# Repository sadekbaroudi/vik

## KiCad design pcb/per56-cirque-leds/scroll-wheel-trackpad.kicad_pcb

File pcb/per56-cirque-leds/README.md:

# PER56 Scroll Ring with Cirque Trackpad and LEDs

## Overview

This is a VIK module designed to mount a [PER56 scroll ring](https://www.mouser.com/new/bourns/bourns-per56-incremental-ring-encoders/), with a 35mm [Cirque Trackpad](https://www.cirque.com/glidepoint-circle-trackpads) and optional WS2812B LEDs.

This was used to demonstrate a build for [vulpes minora](https://github.com/sadekbaroudi/vulpes-minora). See the repo for pictures.

## Fabrication and BOM

For PCB fabrication, you can use the files in the production folder.

* gerbers.zip - the file used to fabricate the pcb
* bom.csv - used for PCBA. You can also use the part numbers in this file to look up the exact parts as [lcsc.com](https://lcsc.com)
* positions.csv - used for PCBA

Using the 3 files above, this has been tested at [jlcpcb.com](https://jlcpcb.com)

## VIK module certification

| Category                | Classification          | Response           |
| ----------------------- | ----------------------- | ------------------ |
| FPC connector           | Required                | :heavy_check_mark: |
| Breakout pins           | Recommended             | :x:                |
| Uses: SPI               | Optional                | :heavy_check_mark: |
| SPI used for SPI only   | Strongly recommended    | :heavy_check_mark: |
| Uses: I2C               | Optional                | :x:                |
| I2C used for I2C only   | Strongly Recommended    | N/A                |
| I2C pull ups            | Required                | N/A                |
| Uses: RGB               | Optional                | :heavy_check_mark: |
| Uses: Extra GPIO 1      | Optional                | :heavy_check_mark: |
| Uses: Extra GPIO 2      | Optional                | :heavy_check_mark: |
| Standard PCB Size/Mount | Strongly recommended    | Large              |

## PCB images

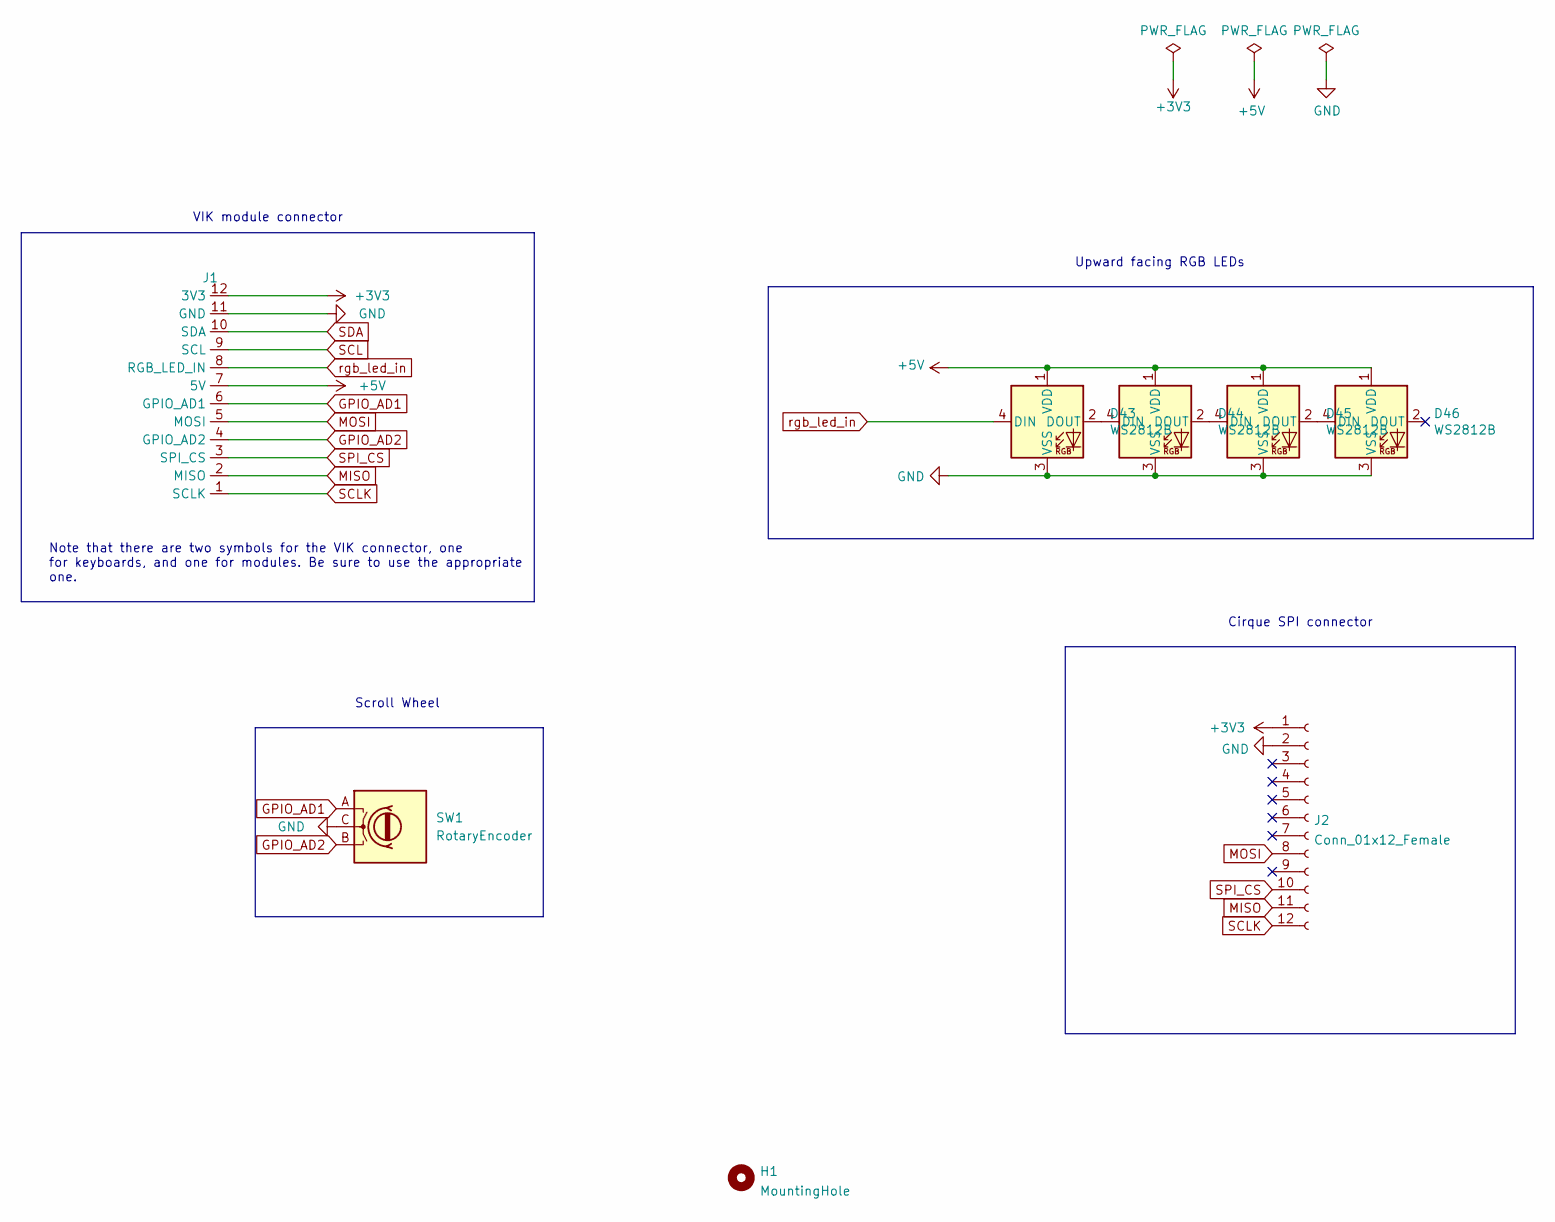
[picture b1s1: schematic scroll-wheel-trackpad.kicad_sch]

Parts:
D43, D44, D45, D46: WS2812B; LED_WS2812B_PLCC4_5.0x5.0mm_P3.2mm-reversible; LCSC C2761795
H1: MountingHole; vik-module-mounting-large
J1: vik-module-connector-horizontal; LCSC C479750
J2: Conn_01x12_Female; FPC-SMD_FPC05012-09200-.5mm-rev; LCSC C479750
SW1: RotaryEncoder; PERS56v3

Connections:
+3V3: J1.12 (3V3), J2.1
+5V: D43.1 (VDD), D44.1 (VDD), D45.1 (VDD), D46.1 (VDD), J1.7 (5V)
GND: D43.3 (VSS), D44.3 (VSS), D45.3 (VSS), D46.3 (VSS), J1.11 (GND), J2.2, SW1.C
GPIO_AD1: J1.6 (GPIO_AD1), SW1.A
GPIO_AD2: J1.4 (GPIO_AD2), SW1.B
MISO: J1.2 (MISO), J2.11
MOSI: J1.5 (MOSI), J2.8
unnamed: D43.2 (DOUT), D44.4 (DIN)
unnamed: D44.2 (DOUT), D45.4 (DIN)
unnamed: D45.2 (DOUT), D46.4 (DIN)
SCL: J1.9 (SCL)
SCLK: J1.1 (SCLK), J2.12
SDA: J1.10 (SDA)
SPI_CS: J1.3 (SPI_CS), J2.10
rgb_led_in: D43.4 (DIN), J1.8 (RGB_LED_IN)

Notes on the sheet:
Cirque SPI connector
Upward facing RGB LEDs
VIK module connector
Note that there are two symbols for the VIK connector, one for keyboards, and one for modules. Be sure to use the appropriate one.
Scroll Wheel

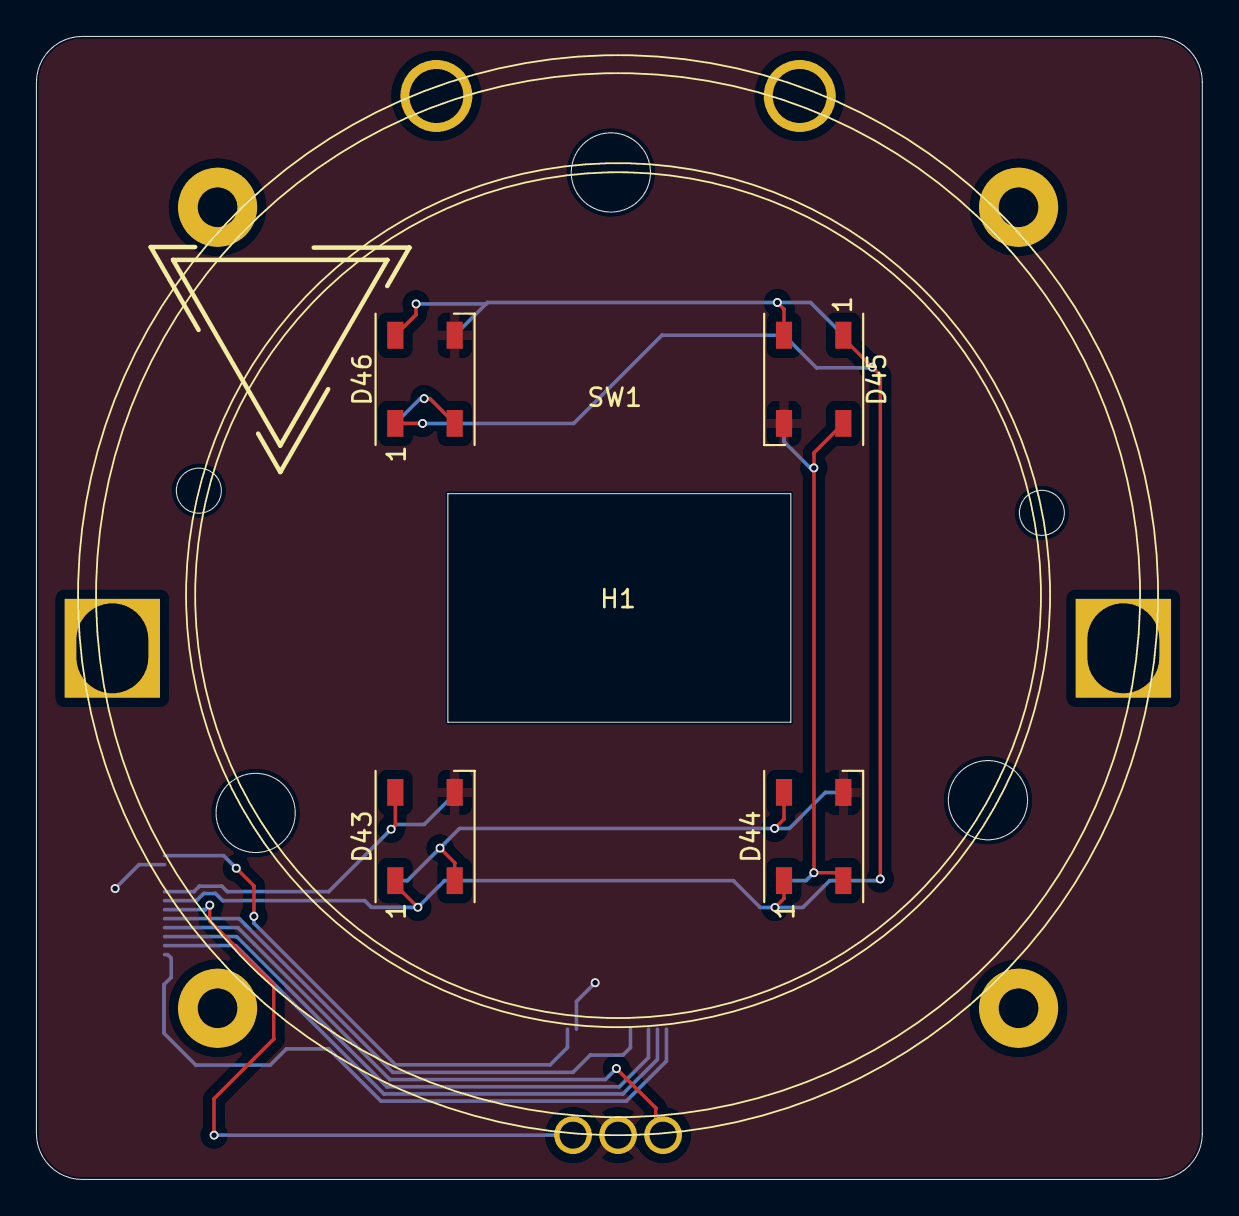
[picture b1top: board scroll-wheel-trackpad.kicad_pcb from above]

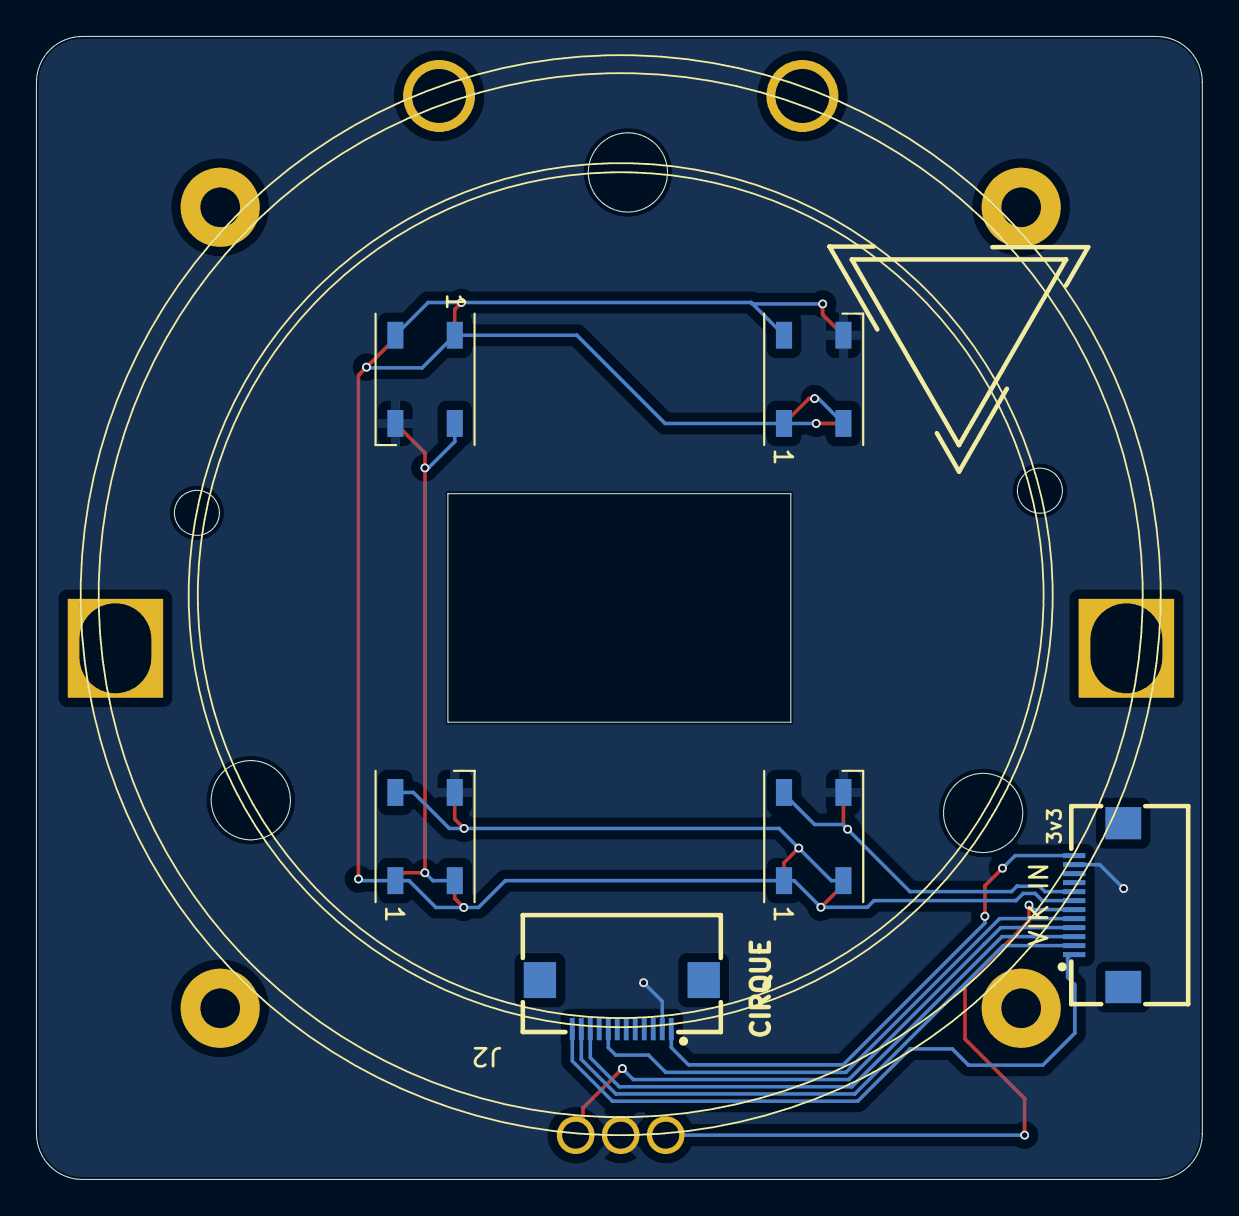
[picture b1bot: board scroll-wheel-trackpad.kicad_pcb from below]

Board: 2 copper layers, 64.8 x 63.5 mm, 8 parts (2 on the bottom side), 13 nets.

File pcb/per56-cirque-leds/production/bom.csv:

Designator,Footprint,Quantity,Value,LCSC Part #
"D43, D44, D45, D46",LED_WS2812B_PLCC4_5.0x5.0mm_P3.2mm-reversible,4,WS2812B,C2761795
H1,vik-module-mounting-large,1,MountingHole,
J1,vik-module-connector-horizontal,1,~,C479750
J2,FPC-SMD_FPC05012-09200-.5mm-rev,1,Conn_01x12_Female,C479750
SW1,PERS56v3,1,RotaryEncoder,

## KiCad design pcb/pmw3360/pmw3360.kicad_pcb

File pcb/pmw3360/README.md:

# PMW3360 trackball pcb

## Overview

This is a VIK module to use a PMW3360 motion sensor. This sensor is primarily used for mousing applications, and is supported in [QMK](https://github.com/qmk_firmware/qmk)

The most common use in the keyboard community is for trackballs.

Note that while I2C, RGB, and extra GPIO are broken out, but are not used in the circuitry, so they are not needed for the sensor. There are also footprints for I2C pull up resistors, which are also not needed, as I2C is not used.

## Fabrication and BOM

For PCB fabrication, you can use the files in the production folder.

* gerbers.zip - the file used to fabricate the pcb
* bom.csv - used for PCBA. You can also use the part numbers in this file to look up the exact parts as [lcsc.com](https://lcsc.com)
* positions.csv - used for PCBA

Using the 3 files above, this has been tested at [jlcpcb.com](https://jlcpcb.com)

## VIK module certification

| Category                | Classification          | Response           |
| ----------------------- | ----------------------- | ------------------ |
| FPC connector           | Required                | :heavy_check_mark: |
| Breakout pins           | Recommended             | :heavy_check_mark: |
| Uses: SPI               | Optional                | :heavy_check_mark: |
| SPI used for SPI only   | Strongly recommended    | :heavy_check_mark: |
| Uses: I2C               | Optional                | :x:                |
| I2C used for I2C only   | Strongly Recommended    | :x:                |
| I2C pull ups            | Required                | N/A                |
| Uses: RGB               | Optional                | :x:                |
| Uses: Extra GPIO 1      | Optional                | :x:                |
| Uses: Extra GPIO 2      | Optional                | :x:                |
| Standard PCB Size/Mount | Strongly recommended    | Small              |

## PCB images

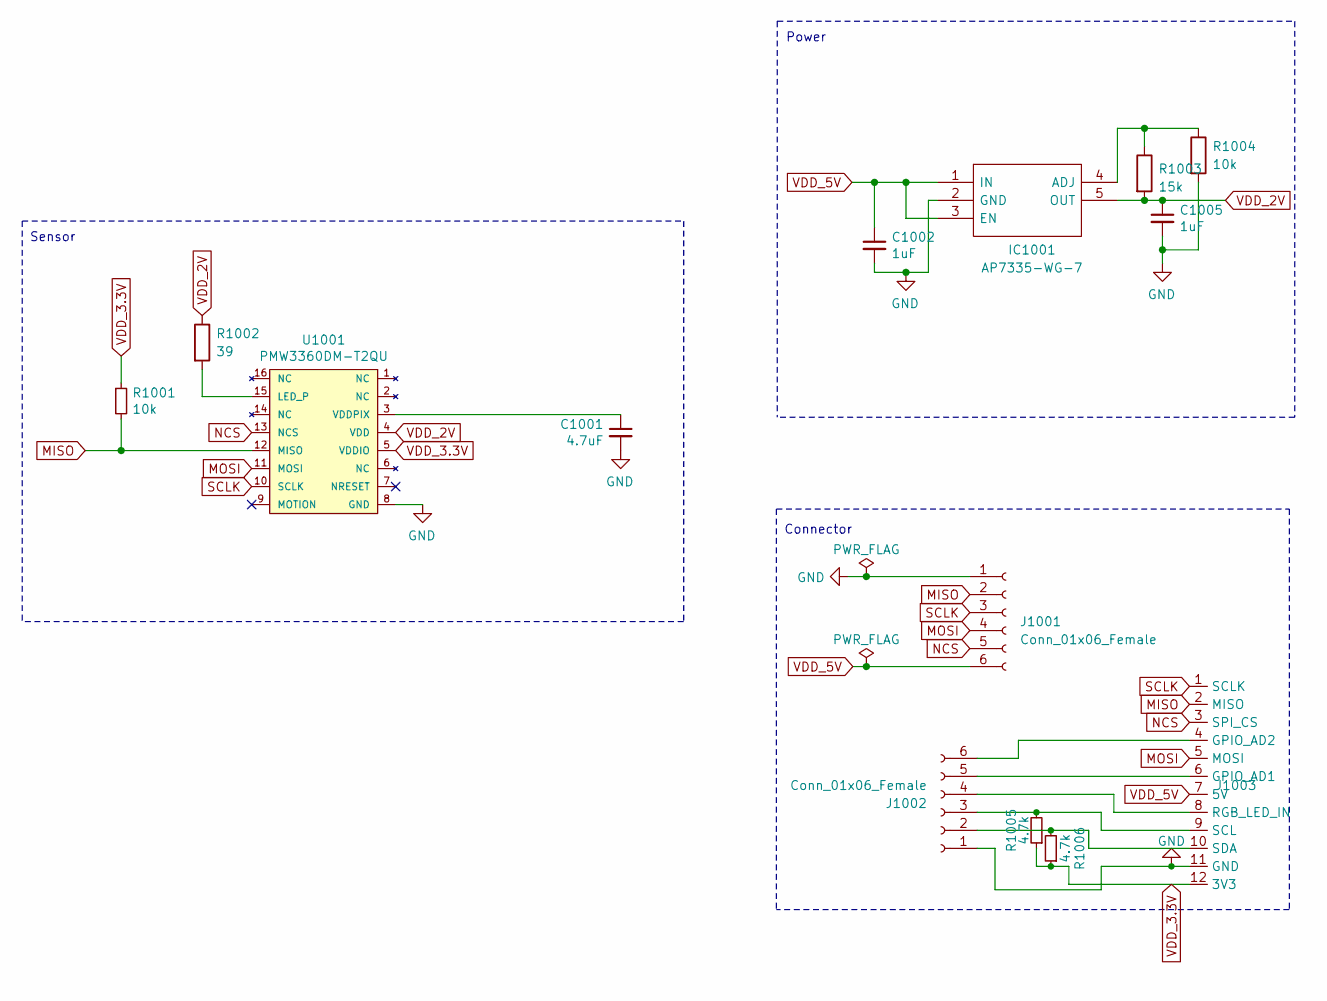
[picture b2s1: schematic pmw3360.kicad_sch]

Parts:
C1001: 4.7uF; C_0603_1608Metric; LCSC C19666
C1002, C1005: 1uF; C_0603_1608Metric; LCSC C15849
IC1001: AP7335-WG-7; SOT-23-5_HandSoldering; Manufacturer_Part_Number AP7331-WG-7; Mouser Part Number 621-AP7331-WG-7
J1001, J1002: Conn_01x06_Female; PinHeader_1x06_P2.54mm_Vertical
J1003: vik-module-connector-horizontal; LCSC C479750
R1001, R1004: 10k; R_0603_1608Metric; LCSC C25804
R1002: 39; R_0603_1608Metric; LCSC C23154
R1003: 15k; R_0603_1608Metric; LCSC C22809
R1005, R1006: 4.7k; D3_TH_SMD
U1001: PMW3360DM-T2QU; DIP-16_W10.16mm

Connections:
GND: C1001.2, C1002.2, C1005.2, IC1001.2 (GND), J1001.1, J1002.1, J1003.11 (GND), R1004.2, U1001.8 (GND)
MISO: J1001.2, J1003.2 (MISO), R1001.2, U1001.12 (MISO)
MOSI: J1001.4, J1003.5 (MOSI), U1001.11 (MOSI)
NCS: J1001.5, J1003.3 (SPI_CS), U1001.13 (NCS)
unnamed: IC1001.4 (ADJ), R1003.1, R1004.1
unnamed: J1002.2, J1003.10 (SDA), R1006.2
unnamed: J1002.3, J1003.9 (SCL), R1005.2
unnamed: J1002.4, J1003.8 (RGB_LED_IN)
unnamed: J1002.5, J1003.6 (GPIO_AD1)
unnamed: J1002.6, J1003.4 (GPIO_AD2)
unnamed: R1002.2, U1001.15 (LED_P)
unnamed: C1001.1, U1001.3 (VDDPIX)
SCLK: J1001.3, J1003.1 (SCLK), U1001.10 (SCLK)
VDD_2V: C1005.1, IC1001.5 (OUT), R1002.1, R1003.2, U1001.4 (VDD)
VDD_3.3V: J1003.12 (3V3), R1001.1, R1005.1, R1006.1, U1001.5 (VDDIO)
VDD_5V: C1002.1, IC1001.1 (IN), IC1001.3 (EN), J1001.6, J1003.7 (5V)

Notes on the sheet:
Power
Sensor
Connector

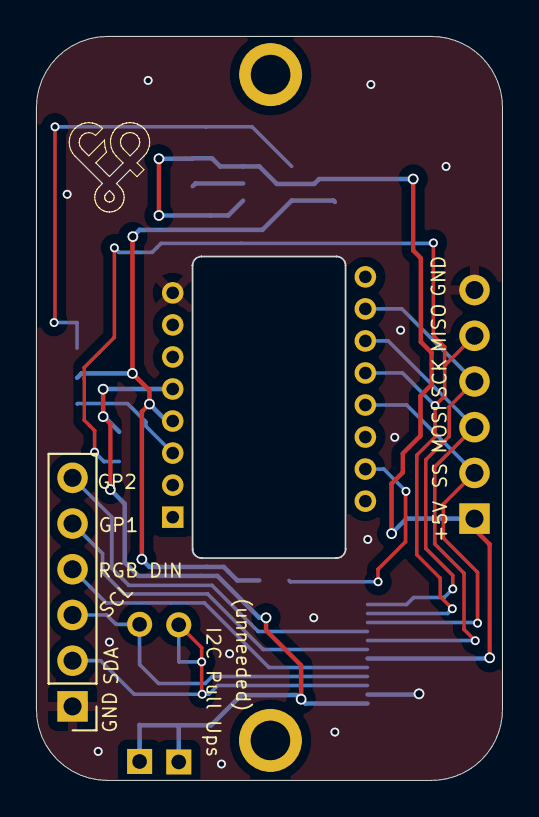
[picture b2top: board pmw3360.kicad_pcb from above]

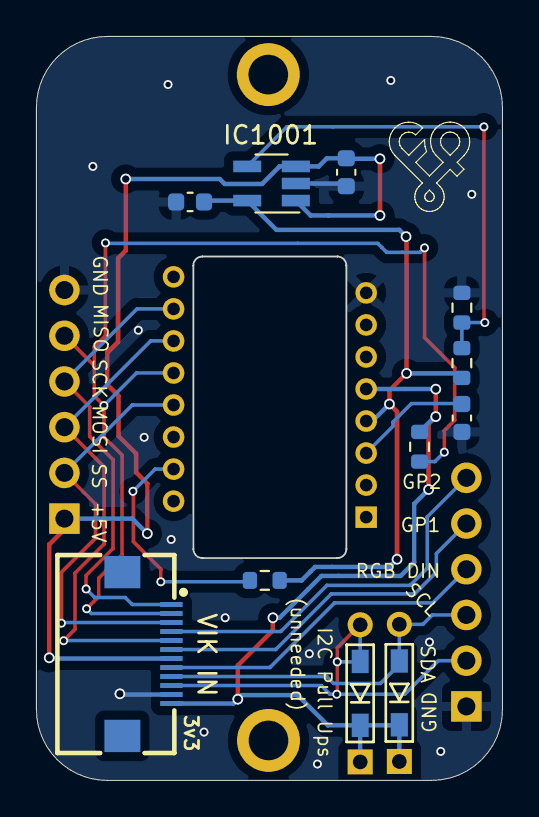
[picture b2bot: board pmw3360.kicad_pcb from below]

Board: 2 copper layers, 25.9 x 41.3 mm, 14 parts (12 on the bottom side), 16 nets.

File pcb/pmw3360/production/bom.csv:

Designator,Footprint,Quantity,Value,LCSC Part #
"_2, ",,2,,
C1001,0603,1,4.7uF,C19666
"C1002, C1005",0603,2,1uF,C15849
IC1001,SOT-23-5_HandSoldering,1,AP7335-WG-7,C460382
"J1001, J1002",PinHeader_1x06_P2.54mm_Vertical,2,Conn_01x06_Female,
J1003,vik-module-connector-horizontal,1,~,C479750
"R1001, R1004",0603,2,10k,C25804
R1002,0603,1,39,C23154
R1003,0603,1,15k,C22809
"R1005, R1006",D3_TH_SMD,2,4.7k,
U1001,DIP-16_W10.16mm,1,PMW3360DM-T2QU,

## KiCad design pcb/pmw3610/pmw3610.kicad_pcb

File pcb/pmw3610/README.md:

# PMW3610 trackball pcb

## Overview

This is a VIK module to use a PMW3610 motion sensor. This sensor is primarily used for mousing applications.

The most common use in the keyboard community is for trackballs.

Note that while I2C, RGB, and extra GPIO are broken out, but are not used in the circuitry, so they are not needed for the sensor. There are also footprints for I2C pull up resistors, which are also not needed, as I2C is not used.

There is a jumper for NRESET, with an option to:  
* Route to 3.3V, which means that it's inactive
* Route to the VIK GPIO 1, which allows you to control the state with the connected controller

You do not need to solder the jumper at all, since there is a weak pull up resistor in the PMW3610, but if you have any trouble with the state, and want to explicitly attach to 3.3V, you can.

## IMPORTANT

The PMW3610 sensor is a low power sensor, and uses serial data communication with a motion status pin (to reduce power consumption). This pcb uses the SPI pins, but is not standard SPI communication. This means that you cannot connect this module to a controller or board that uses the VIK SPI pins for any other purpose. These are being treated as standard GPIO for this module. This is not a VIK compliant module!

That said, if you understand the above, you can still use this module with no issues.

## Alternate parts

The LDO seems to be frequently out of stock at JLCPCB. The part number specified in this module is `C146366`. As an alternate part, you can try to use `C2862411` or `C2869109` (`TLV70019DDCR` or `TLV70019DDCT`, respectively)

## Fabrication and BOM

For PCB fabrication, you can use the files in the production folder.

* gerbers.zip - the file used to fabricate the pcb
* bom.csv - used for PCBA. You can also use the part numbers in this file to look up the exact parts as [lcsc.com](https://lcsc.com)
* positions.csv - used for PCBA

Using the 3 files above, this has been tested at [jlcpcb.com](https://jlcpcb.com)

## VIK module certification

| Category                | Classification          | Response           |
| ----------------------- | ----------------------- | ------------------ |
| FPC connector           | Required                | :heavy_check_mark: |
| Breakout pins           | Recommended             | :heavy_check_mark: |
| Uses: SPI               | Optional                | :heavy_check_mark: |
| SPI used for SPI only   | Strongly recommended    | :x:                |
| Uses: I2C               | Optional                | :x:                |
| I2C used for I2C only   | Strongly Recommended    | :x:                |
| I2C pull ups            | Required                | N/A                |
| Uses: RGB               | Optional                | :x:                |
| Uses: Extra GPIO 1      | Optional                | :x:                |
| Uses: Extra GPIO 2      | Optional                | :x:                |
| Standard PCB Size/Mount | Strongly recommended    | Small              |

## PCB images

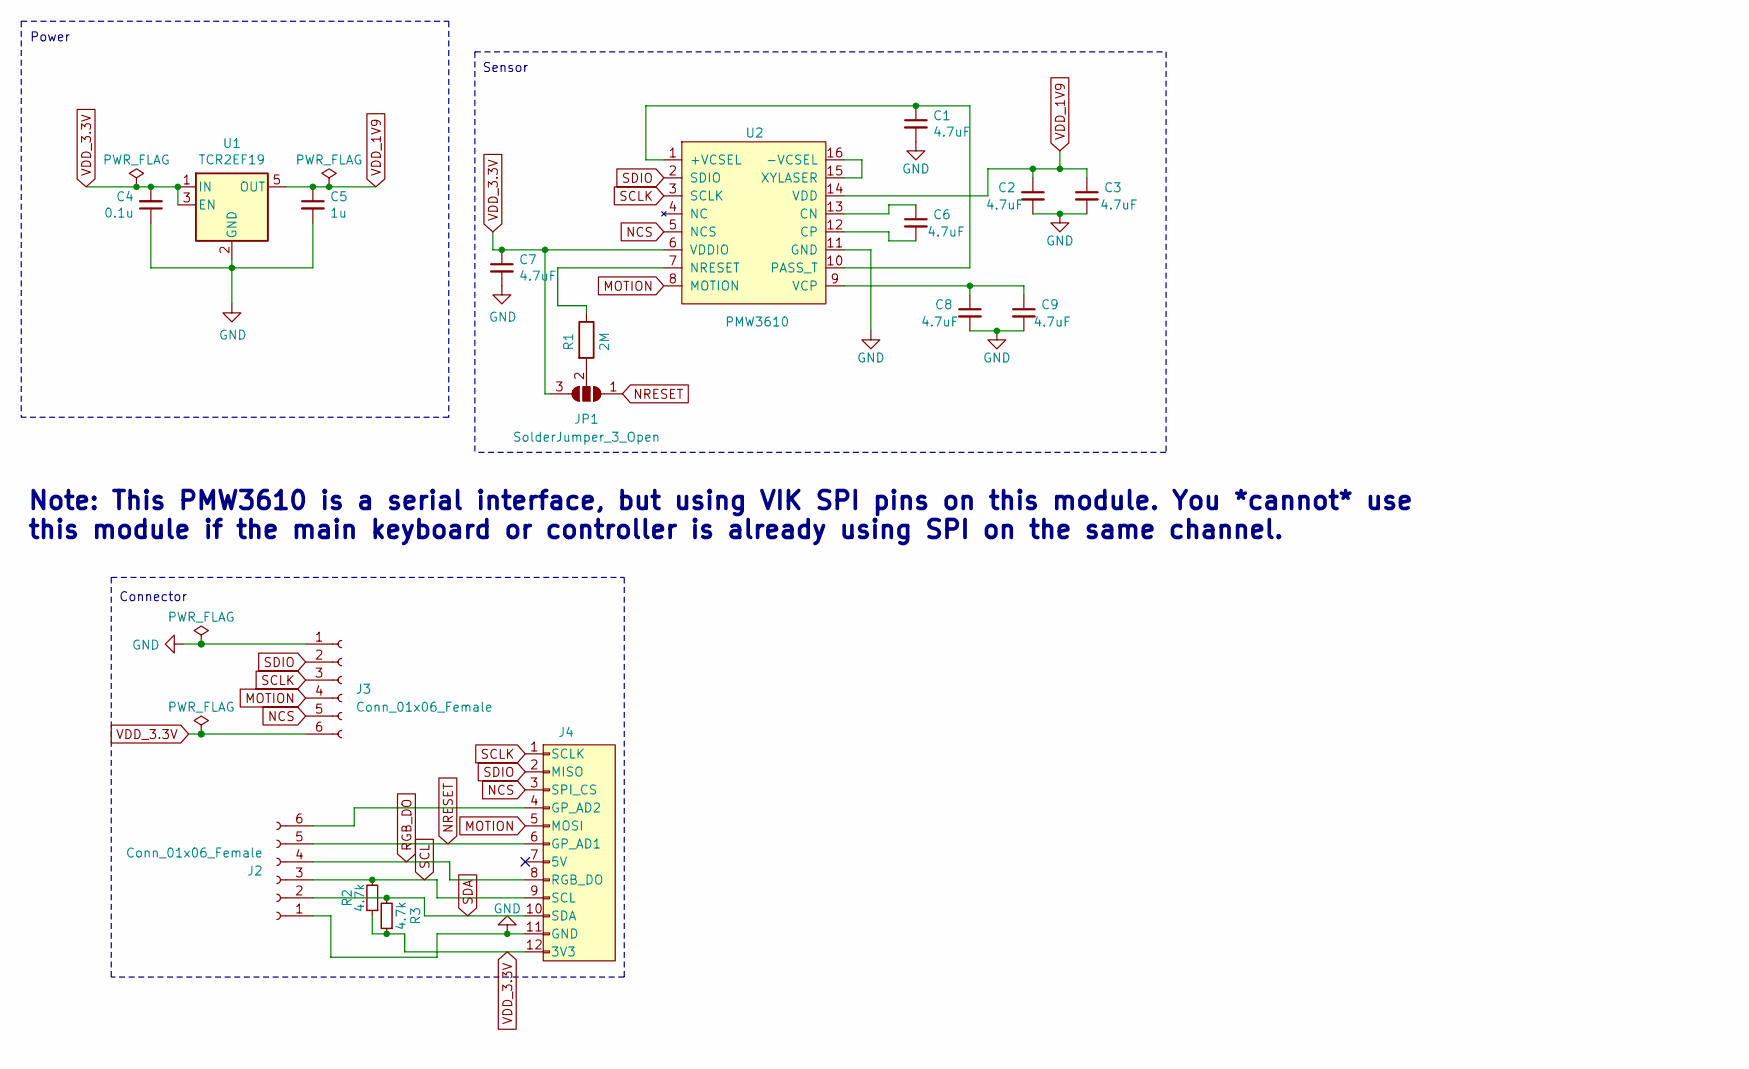
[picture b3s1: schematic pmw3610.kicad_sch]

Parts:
C1, C2, C3, C6, C7, C8, C9: 4.7uF; C_0603_1608Metric; LCSC C19666
C4: 0.1u; C_0603_1608Metric; LCSC C14663
C5: 1u; C_0603_1608Metric; LCSC C15849
J2, J3: Conn_01x06_Female; PinHeader_1x06_P2.54mm_Vertical
J4: vik-module-connector-horizontal; LCSC C479750
JP1: SolderJumper_3_Open; SolderJumper-3_P1.3mm_Open_RoundedPad1.0x1.5mm_NumberLabels
R1: 2M; R_0603_1608Metric; LCSC C465466
R2, R3: 4.7k; D3_TH_SMD
U1: TCR2EF19; SOT-23-5; LCSC C146366
U2: PMW3610

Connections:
GND: C1.2, C2.2, C3.2, C4.1, C5.2, C7.2, C8.2, C9.2, J2.1, J3.1, J4.11 (GND), U1.2 (GND), U2.11 (GND)
MOTION: J3.4, J4.5 (MOSI), U2.8 (MOTION)
NCS: J3.5, J4.3 (SPI_CS), U2.5 (NCS)
NRESET: J2.5, J4.6 (GP_AD1), JP1.1 (A)
unnamed: J2.6, J4.4 (GP_AD2)
unnamed: JP1.2 (C), R1.2
unnamed: C1.1, U2.1 (+VCSEL), U2.10 (PASS_T)
unnamed: U2.15 (XYLASER), U2.16 (-VCSEL)
unnamed: C6.1, U2.13 (CN)
unnamed: C6.2, U2.12 (CP)
unnamed: R1.1, U2.7 (NRESET)
unnamed: C8.1, C9.1, U2.9 (VCP)
RGB_DO: J2.4, J4.8 (RGB_DO)
SCL: J2.3, J4.9 (SCL), R2.2
SCLK: J3.3, J4.1 (SCLK), U2.3 (SCLK)
SDA: J2.2, J4.10 (SDA), R3.2
SDIO: J3.2, J4.2 (MISO), U2.2 (SDIO)
VDD_1V9: C2.1, C3.1, C5.1, U1.5 (OUT), U2.14 (VDD)
VDD_3.3V: C4.2, C7.1, J3.6, J4.12 (3V3), JP1.3 (B), R2.1, R3.1, U1.1 (IN), U1.3 (EN), U2.6 (VDDIO)

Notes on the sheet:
Connector
Power
Note: This PMW3610 is a serial interface, but using VIK SPI pins on this module. You *cannot* use this module if the main keyboard or controller is already using SPI on the same channel.
Sensor

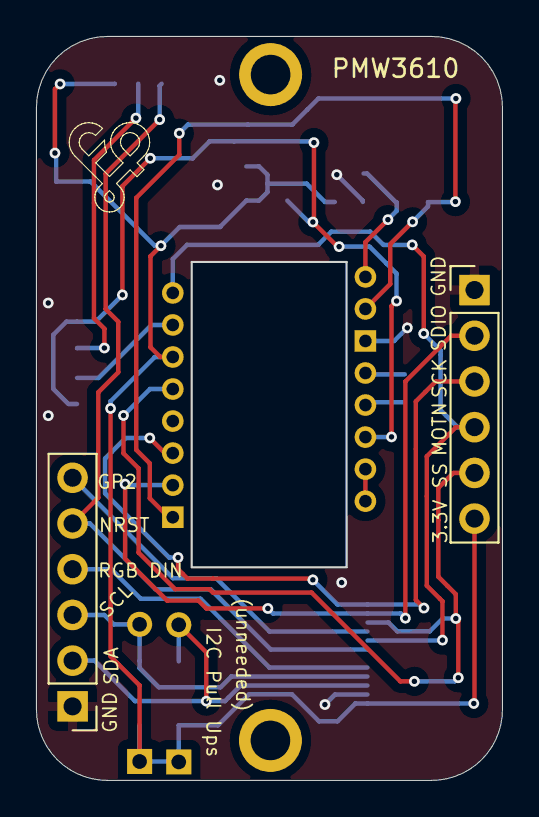
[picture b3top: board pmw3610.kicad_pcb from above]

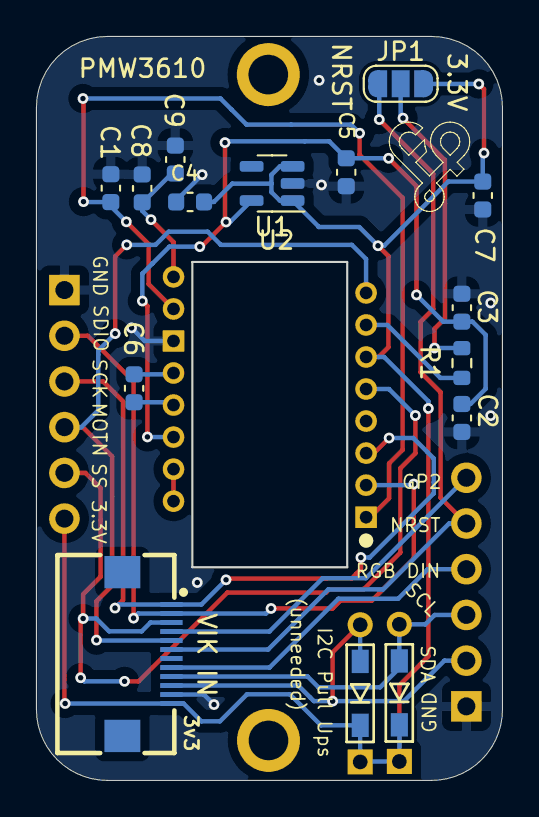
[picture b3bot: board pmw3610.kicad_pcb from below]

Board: 2 copper layers, 25.9 x 41.3 mm, 18 parts (16 on the bottom side), 19 nets.

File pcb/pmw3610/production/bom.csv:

Designator,Footprint,Quantity,Value,LCSC Part #
"C1, C2, C3, C6, C7, C8, C9",0603,7,4.7uF,C19666
C4,0603,1,0.1u,C14663
C5,0603,1,1u,C15849
"J2, J3",PinHeader_1x06_P2.54mm_Vertical,2,Conn_01x06_Female,
J4,vik-module-connector-horizontal,1,~,C479750
JP1,SolderJumper-3_P1.3mm_Open_RoundedPad1.0x1.5mm_NumberLabels,1,SolderJumper_3_Open,
R1,0603,1,2M,C465466
"R2, R3",D3_TH_SMD,2,4.7k,
U1,SOT-23-5,1,TCR2EF19,C146366
U2,PMW3610,1,PMW3610,

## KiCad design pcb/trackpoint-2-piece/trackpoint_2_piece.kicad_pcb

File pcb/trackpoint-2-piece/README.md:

# Trackpoint 2 piece module

## Overview

This is a VIK module made to connect the [trackpoint 2 piece](https://deskthority.net/wiki/TrackPoint_Hardware#2-piece_Trackpoint) breakout board.

The through holes should be used if connecting this to a controller that uses 5v logic. The VIK connector is assumed to be connecting to a 3.3v controller, so the logic levels are 3.3v.

The overall design is as follows:
* VIK uses 3.3V, so the 3.3V through holes all goes to the VIK connector, since VIK expects 3.3V logic.
* The mosfets (etc) convert the 3.3V logic to 5V logic (and the other way around), so none of the 5V through holes are connected to the VIK connector. The trackpoint expects 5V logic
* The 5V logic is all connected directly to the trackpoint, since as mentioned, the trackpoint expects 5V, and VIK does not

The general usage of this is:
* If you are connecting to a 5V controller, you just use the 5V through holes. You can't use the VIK connector
* If you are connecting to a 3.3V controller, you can use either VIK connector or the 3.3V through holes

## Fabrication and BOM

For PCB fabrication, you can use the files in the production folder.

* gerbers.zip - the file used to fabricate the pcb
* bom.csv - used for PCBA. You can also use the part numbers in this file to look up the exact parts as [lcsc.com](https://lcsc.com)
* positions.csv - used for PCBA

Using the 3 files above, this has been tested at [jlcpcb.com](https://jlcpcb.com)

## VIK module certification

| Category                | Classification          | Response           |
| ----------------------- | ----------------------- | ------------------ |
| FPC connector           | Required                | :heavy_check_mark: |
| Breakout pins           | Recommended             | :x:                |
| Uses: SPI               | Optional                | :x:                |
| SPI used for SPI only   | Strongly recommended    | N/A                |
| Uses: I2C               | Optional                | :x:                |
| I2C used for I2C only   | Strongly Recommended    | :x:                |
| I2C pull ups            | Required                | :x:                |
| Uses: RGB               | Optional                | :x:                |
| Uses: Extra GPIO 1      | Optional                | :heavy_check_mark: |
| Uses: Extra GPIO 2      | Optional                | :heavy_check_mark: |
| Standard PCB Size/Mount | Strongly recommended    | :x:                |

## PCB images

## Trackpoint module images

## Credit

Thank you to crehmann for testing this module with their design of the following keyboard, clear instructions and images. This was monumentally helpful in getting this ironed out quickly:  
https://github.com/crehmann/TPS42  

Thanks to quappo for doing the research on existing solutions for trackpoint connectivity  

Thanks to Pete Johanson for adding the logic level conversion circuitry.  

Images: from https://deskauthority.net/wiki/TrackPoint_Hardware

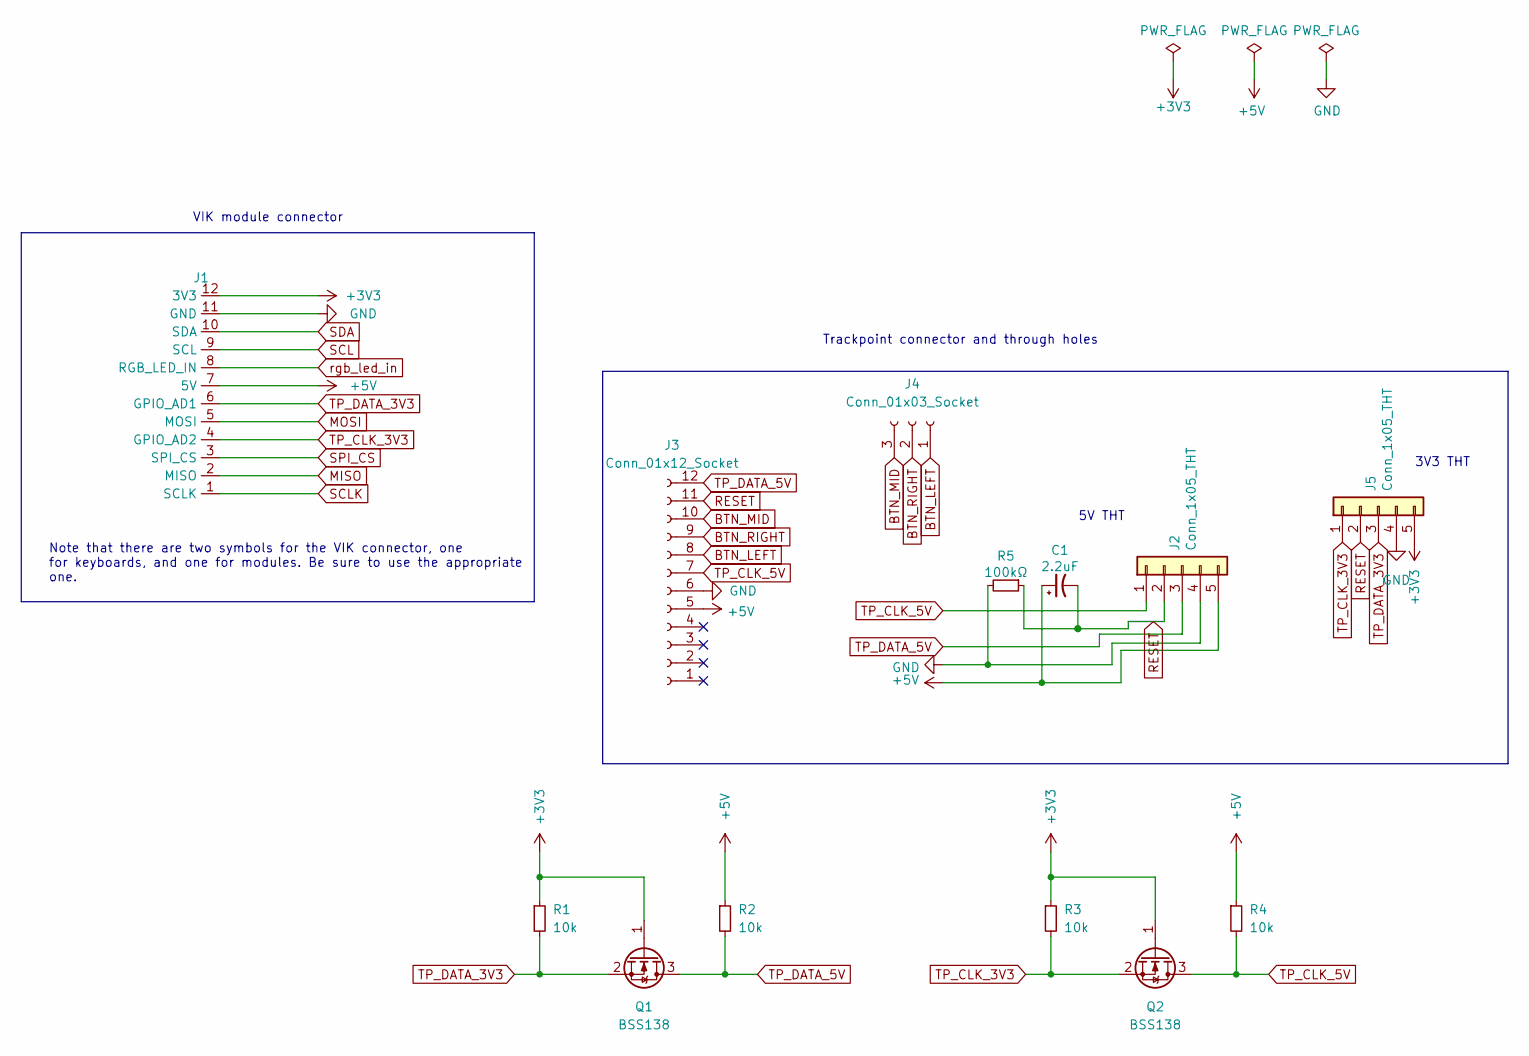
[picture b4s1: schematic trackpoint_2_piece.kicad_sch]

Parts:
C1: 2.2uF; C_0805_2012Metric_Pad1.18x1.45mm_HandSolder; LCSC C377773
J1: vik-module-connector-horizontal; LCSC C479750
J2, J5: Conn_1x05_THT; Connector_THT_1x5_2.54
J3: Conn_01x12_Socket; TE_1-84953-2_1x12-1MP_P1.0mm_Horizontal; LCSC C262367
J4: Conn_01x03_Socket; Connector_THT_1x3_2.54
Q1, Q2: BSS138; SOT-23; LCSC C78284
R1, R2, R3, R4: 10k; R_0805_2012Metric_Pad1.20x1.40mm_HandSolder; LCSC C17414
R5: 100kΩ; R_0805_2012Metric_Pad1.20x1.40mm_HandSolder; LCSC C149504

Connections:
+3V3: J1.12 (3V3), J5.5, Q1.1 (G), Q2.1 (G), R1.1, R3.1
+5V: C1.1, J1.7 (5V), J2.5, J3.5, R2.1, R4.1
BTN_LEFT: J3.8, J4.1
BTN_MID: J3.10, J4.3
BTN_RIGHT: J3.9, J4.2
GND: J1.11 (GND), J2.4, J3.6, J5.4, R5.2
MISO: J1.2 (MISO)
MOSI: J1.5 (MOSI)
RESET: C1.2, J2.2, J3.11, J5.2, R5.1
SCL: J1.9 (SCL)
SCLK: J1.1 (SCLK)
SDA: J1.10 (SDA)
SPI_CS: J1.3 (SPI_CS)
TP_CLK_3V3: J1.4 (GPIO_AD2), J5.1, Q2.2 (S), R3.2
TP_CLK_5V: J2.1, J3.7, Q2.3 (D), R4.2
TP_DATA_3V3: J1.6 (GPIO_AD1), J5.3, Q1.2 (S), R1.2
TP_DATA_5V: J2.3, J3.12, Q1.3 (D), R2.2
rgb_led_in: J1.8 (RGB_LED_IN)

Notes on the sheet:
5V THT
Note that there are two symbols for the VIK connector, one for keyboards, and one for modules. Be sure to use the appropriate one.
VIK module connector
3V3 THT
Trackpoint connector and through holes

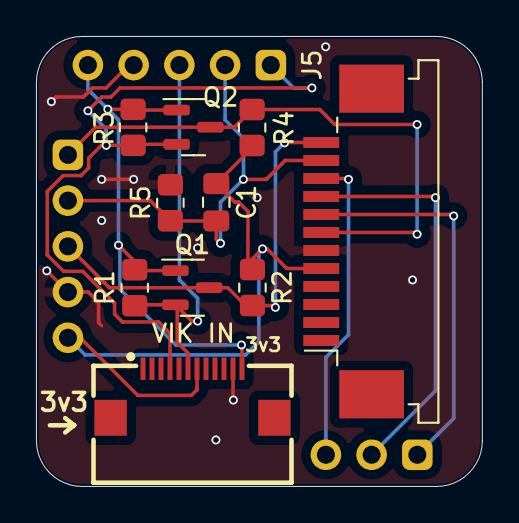
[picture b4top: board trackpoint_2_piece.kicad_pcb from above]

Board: 2 copper layers, 24.8 x 25.0 mm, 13 parts (0 on the bottom side), 11 nets.

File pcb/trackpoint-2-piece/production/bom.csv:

Designator,Footprint,Quantity,Value,LCSC Part #
C1,0805,1,2.2uF,C377773
J1,vik-module-connector-horizontal,1,~,C479750
"J2, J5",Connector_THT_1x5_2.54,2,Conn_1x05_THT,
J3,TE_1-84953-2_1x12-1MP_P1.0mm_Horizontal,1,Conn_01x12_Socket,C262367
J4,Connector_THT_1x3_2.54,1,Conn_01x03_Socket,
"Q1, Q2",SOT-23,2,BSS138,C78284
"R1, R2, R3, R4",0805,4,10k,C17414
R5,0805,1,100kΩ,C149504

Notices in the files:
pcb/pmw3360-xs/pmw3360.kicad_sch:
Copyright Quentin Lebastard
